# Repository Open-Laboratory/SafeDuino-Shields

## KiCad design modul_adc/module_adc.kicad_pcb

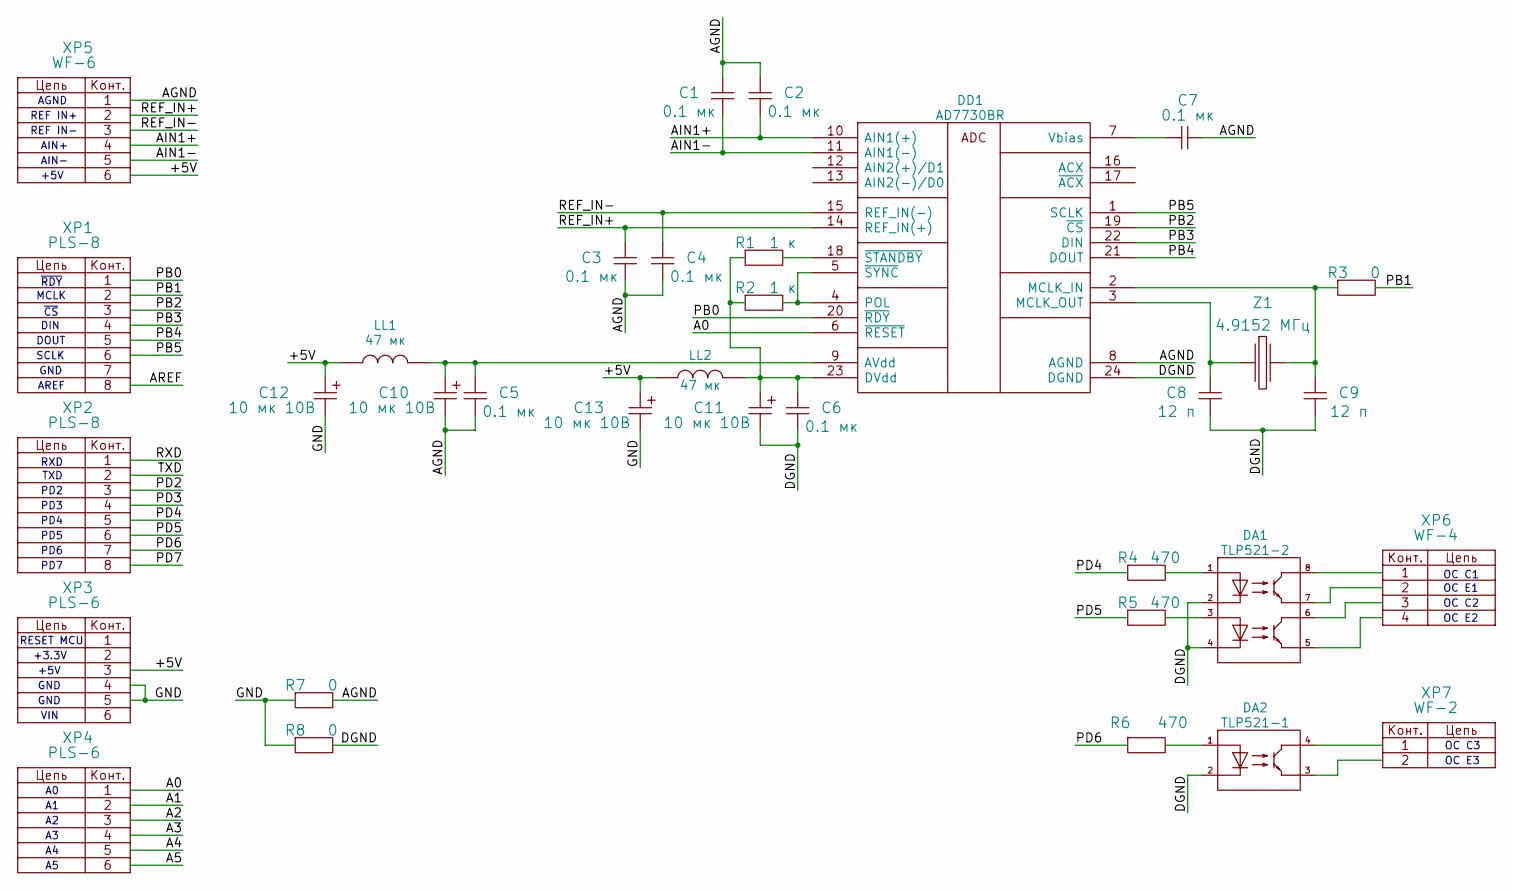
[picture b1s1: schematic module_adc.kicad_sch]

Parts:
C1, C2, C3, C4, C5, C6, C7: 0.1 мк; SMD0805
C8, C9: 12 п; SMD0805
C10, C11, C12, C13: 10 мк 10В; CASE_B
DA1: TLP521-2; DIP_8
DA2: TLP521-1; DIP_4
DD1: AD7730BR; SOIC_24
LL1, LL2: 47 мк; SMD0805
R1, R2: 1 к; SMD0805
R3, R7, R8: 0; SMD0805
R4, R5, R6: 470; SMD0805
XP1, XP2: PLS-8; PIN_ARRAY_8x1
XP3, XP4: PLS-6; PIN_ARRAY_6x1
XP5: WF-6
XP6: WF-4
XP7: WF-2
Z1: 4.9152 МГц; HC-49U

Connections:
/+5V: C12.1, C13.1, LL1.2, LL2.2, XP3.3, XP5.6
/A0: DD1.6 (~RESET), XP4.1
/A1: XP4.2
/A2: XP4.3
/A3: XP4.4
/A4: XP4.5
/A5: XP4.6
/AGND: C1.1, C2.1, C3.2, C4.2, C5.2, C7.1, C10.2, DD1.8 (AGND), R7.2, XP5.1
/AIN1+: C2.2, DD1.10 (AIN1(+)), XP5.4
/AIN1-: C1.2, DD1.11 (AIN1(-)), XP5.5
/AREF: XP1.8
/DGND: C6.2, C8.2, C9.2, C11.2, DA1.2, DA1.4, DA2.2, DD1.24 (DGND), R8.2
/GND: C12.2, C13.2, R7.1, R8.1, XP3.4, XP3.5
/PB0: DD1.20 (~RDY), XP1.1
/PB1: R3.2, XP1.2
/PB2: DD1.19 (~CS), XP1.3
/PB3: DD1.22 (DIN), XP1.4
/PB4: DD1.21 (DOUT), XP1.5
/PB5: DD1.1 (SCLK), XP1.6
/PD2: XP2.3
/PD3: XP2.4
/PD4: R4.1, XP2.5
/PD5: R5.1, XP2.6
/PD6: R6.1, XP2.7
/PD7: XP2.8
/REF_IN+: C3.1, DD1.14 (REF_IN(+)), XP5.2
/REF_IN-: C4.1, DD1.15 (REF_IN(-)), XP5.3
/RXD: XP2.1
/TXD: XP2.2
unnamed: DA1.1, R4.2
unnamed: DA1.3, R5.2
unnamed: DA1.5, XP6.4
unnamed: DA1.6, XP6.3
unnamed: DA1.7, XP6.2
unnamed: DA1.8, XP6.1
unnamed: DA2.1, R6.2
unnamed: DA2.3, XP7.2
unnamed: DA2.4, XP7.1
unnamed: C5.1, C10.1, DD1.9 (AVdd), LL1.1
unnamed: C6.1, C11.1, DD1.23 (DVdd), LL2.1, R1.1, R2.1
unnamed: C9.1, DD1.2 (MCLK_IN), R3.1, Z1.2
unnamed: C8.1, DD1.3 (MCLK_OUT), Z1.1
unnamed: DD1.4 (POL), DD1.5 (~SYNC), R2.2
unnamed: C7.2, DD1.7 (Vbias)
unnamed: DD1.18 (~STANDBY), R1.2

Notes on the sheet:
RESET MCU
PD7
PD4
+5V
OC E2
MCLK
OC C3
RXD
REF IN-
TXD
PD6
PD2
OC E1
AGND
VIN
GND
OC C1
AREF
~{CS}
OC E3
AIN-
OC C2
DOUT
AIN+
DIN
PD3
~{RDY}
PD5
+3.3V
REF IN+
SCLK

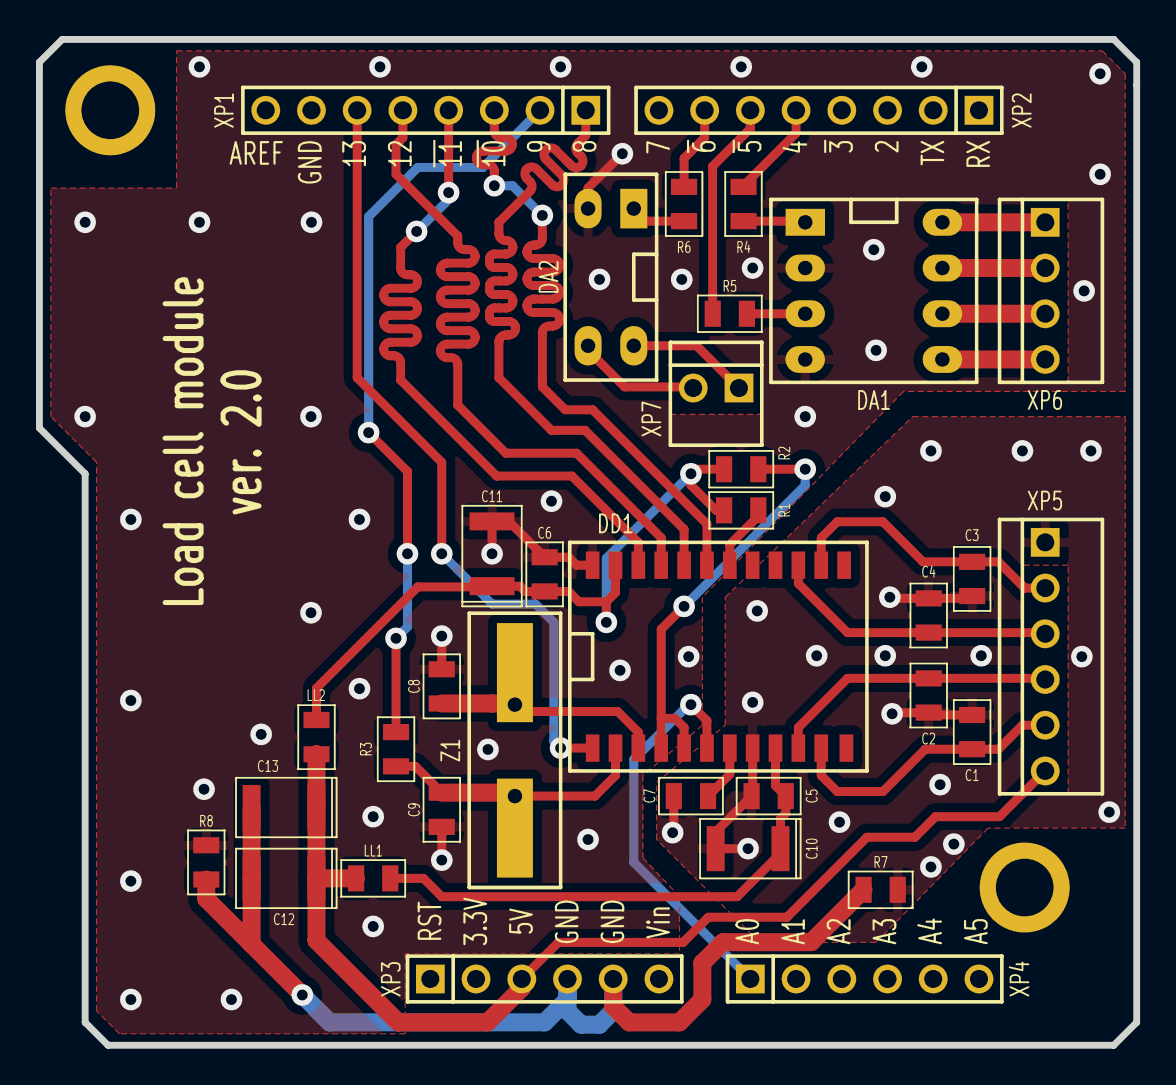
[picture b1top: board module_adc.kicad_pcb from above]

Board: 2 copper layers, 61.0 x 55.9 mm, 36 parts (0 on the bottom side), 34 nets.

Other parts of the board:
1_PIN_3_2mm_1, 1_PIN_3_2mm_2: P***; 1_pin_3_2mm

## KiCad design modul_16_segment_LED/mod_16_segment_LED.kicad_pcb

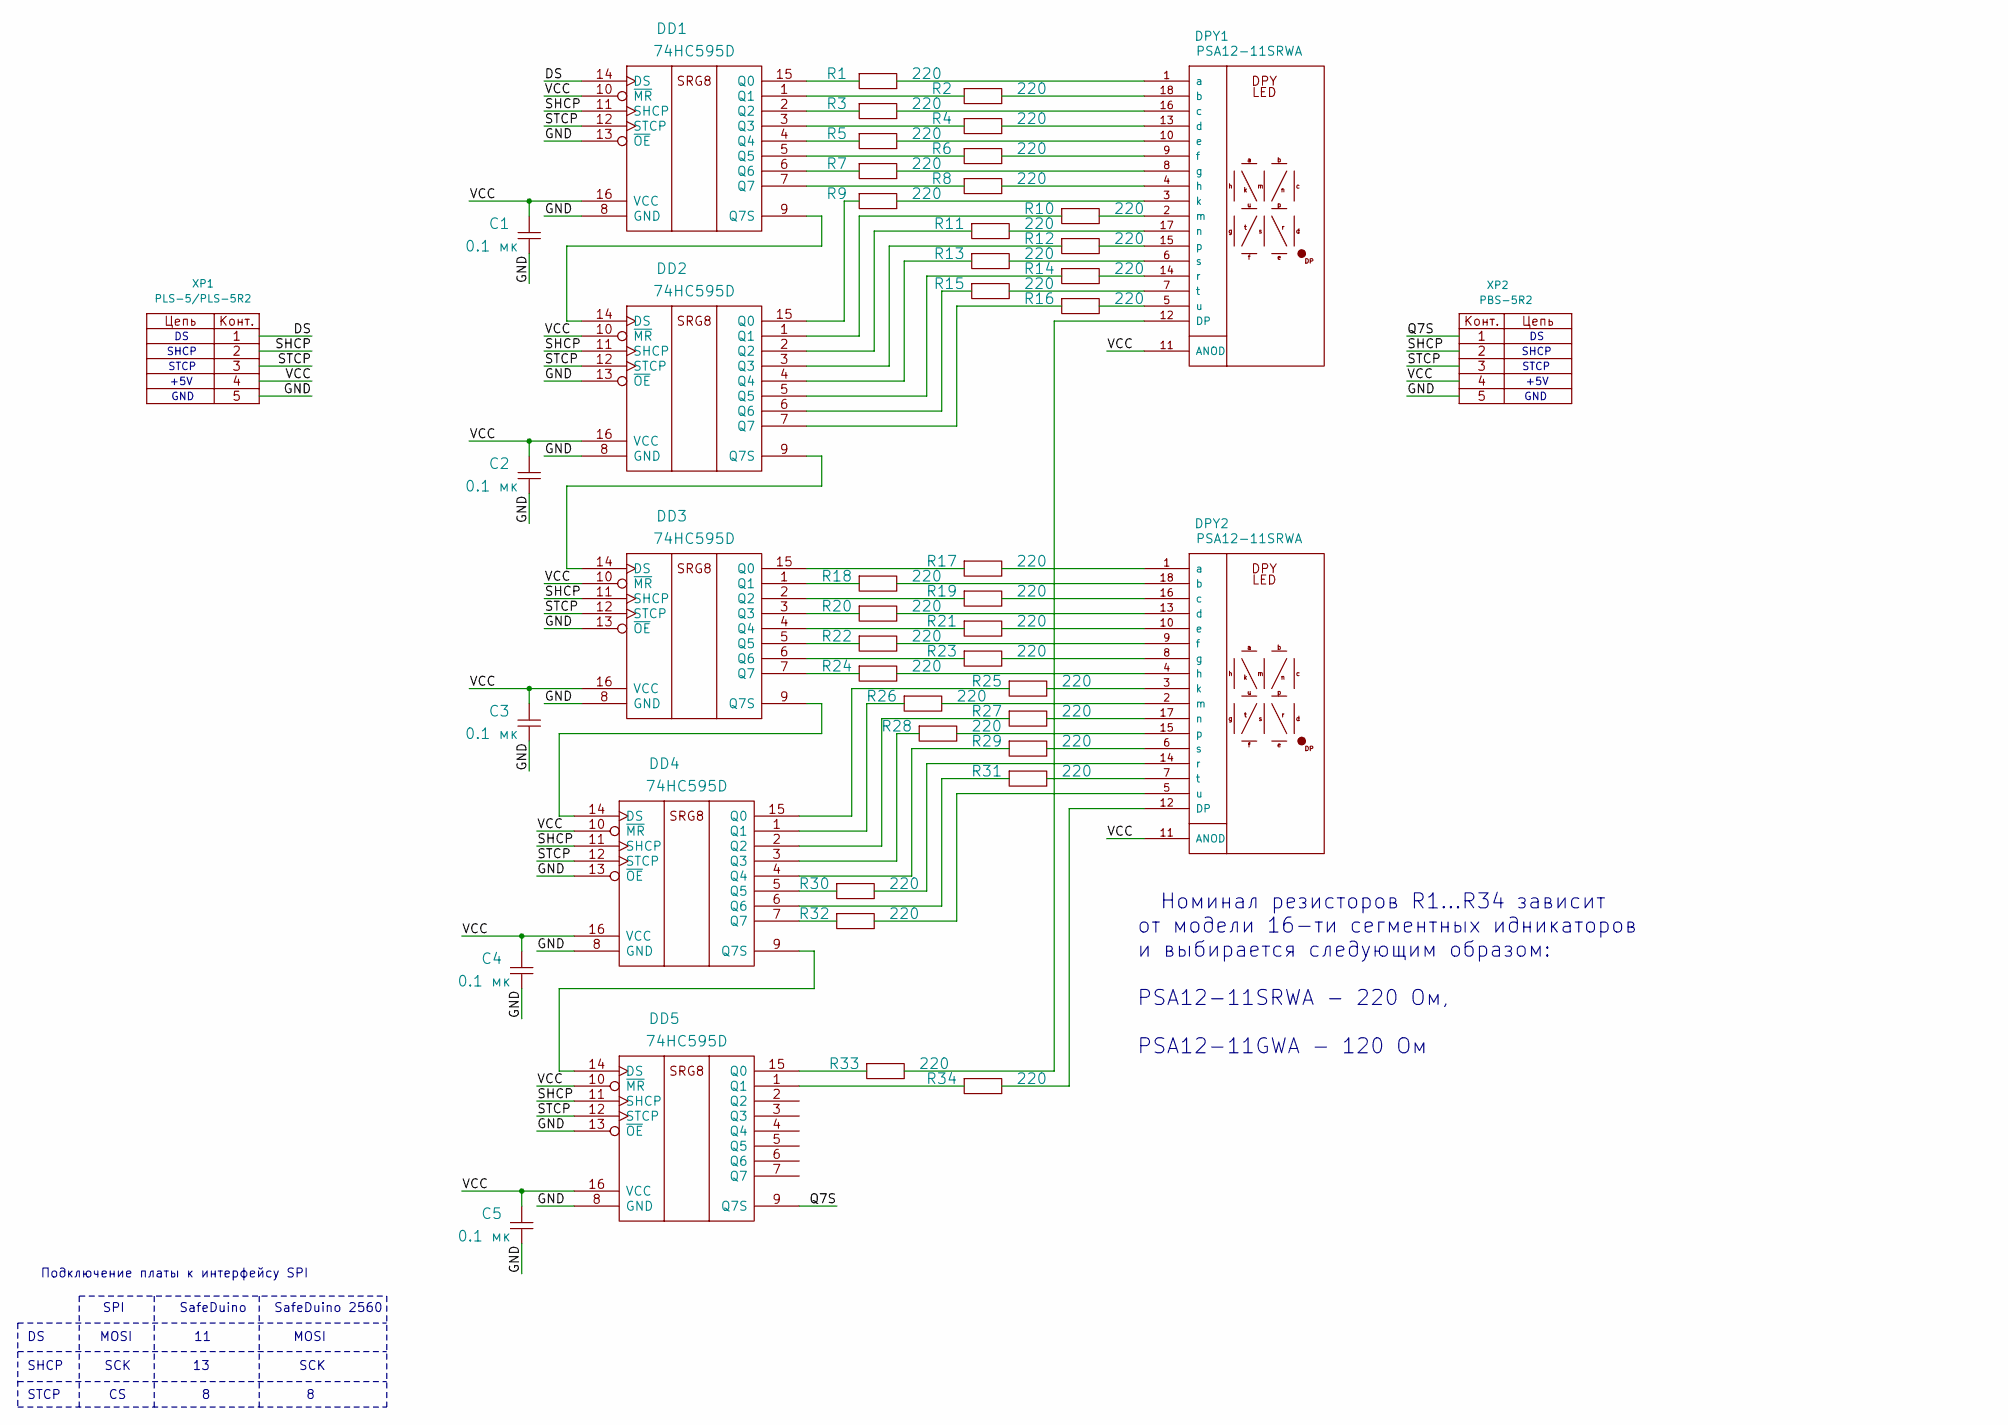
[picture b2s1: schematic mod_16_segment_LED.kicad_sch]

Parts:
C1, C2, C3, C4, C5: 0.1 мк; SMD0805
DD1, DD2, DD3, DD4, DD5: 74HC595D; SOIC16
DPY1, DPY2: PSA12-11SRWA; PSA12-11
R1, R2, R3, R4, R5, R6, R7, R8, R9, R10, R11, R12, R13, R14, R15, R16, R17, R18, R19, R20, R21, R22, R23, R24, R25, R26, R27, R28, R29, R30, R31, R32, R33, R34: 220; SMD0805
XP1: PLS-5/PLS-5R2; PIN_ARRAY_5x1
XP2: PBS-5R2; PIN_ARRAY_5x1

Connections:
/DS: DD1.14 (DS), XP1.1
/GND: C1.1, C2.1, C3.1, C4.1, C5.1, DD1.8 (GND), DD1.13 (~OE), DD2.8 (GND), DD2.13 (~OE), DD3.8 (GND), DD3.13 (~OE), DD4.8 (GND), DD4.13 (~OE), DD5.8 (GND), DD5.13 (~OE), XP1.5, XP2.5
/Q7S: DD5.9 (Q7S), XP2.1
/SHCP: DD1.11 (SHCP), DD2.11 (SHCP), DD3.11 (SHCP), DD4.11 (SHCP), DD5.11 (SHCP), XP1.2, XP2.2
/STCP: DD1.12 (STCP), DD2.12 (STCP), DD3.12 (STCP), DD4.12 (STCP), DD5.12 (STCP), XP1.3, XP2.3
/VCC: C1.2, C2.2, C3.2, C4.2, C5.2, DD1.10 (~MR), DD1.16 (VCC), DD2.10 (~MR), DD2.16 (VCC), DD3.10 (~MR), DD3.16 (VCC), DD4.10 (~MR), DD4.16 (VCC), DD5.10 (~MR), DD5.16 (VCC), DPY1.11 (ANOD), DPY2.11 (ANOD), XP1.4, XP2.4
unnamed: DD1.15 (Q0), R1.1
unnamed: DD1.1 (Q1), R2.1
unnamed: DD1.2 (Q2), R3.1
unnamed: DD1.3 (Q3), R4.1
unnamed: DD1.4 (Q4), R5.1
unnamed: DD1.5 (Q5), R6.1
unnamed: DD1.6 (Q6), R7.1
unnamed: DD1.7 (Q7), R8.1
unnamed: DD1.9 (Q7S), DD2.14 (DS)
unnamed: DD2.15 (Q0), R9.1
unnamed: DD2.1 (Q1), R10.1
unnamed: DD2.2 (Q2), R11.1
unnamed: DD2.3 (Q3), R12.1
unnamed: DD2.4 (Q4), R13.1
unnamed: DD2.5 (Q5), R14.1
unnamed: DD2.6 (Q6), R15.1
unnamed: DD2.7 (Q7), R16.1
unnamed: DD2.9 (Q7S), DD3.14 (DS)
unnamed: DD3.15 (Q0), R17.1
unnamed: DD3.1 (Q1), R18.1
unnamed: DD3.2 (Q2), R19.1
unnamed: DD3.3 (Q3), R20.1
unnamed: DD3.4 (Q4), R21.1
unnamed: DD3.5 (Q5), R22.1
unnamed: DD3.6 (Q6), R23.1
unnamed: DD3.7 (Q7), R24.1
unnamed: DD3.9 (Q7S), DD4.14 (DS)
unnamed: DD4.15 (Q0), R25.1
unnamed: DD4.1 (Q1), R26.1
unnamed: DD4.2 (Q2), R27.1
unnamed: DD4.3 (Q3), R28.1
unnamed: DD4.4 (Q4), R29.1
unnamed: DD4.5 (Q5), R30.1
unnamed: DD4.6 (Q6), R31.1
unnamed: DD4.7 (Q7), R32.1
unnamed: DD4.9 (Q7S), DD5.14 (DS)
unnamed: DD5.15 (Q0), R33.1
unnamed: DD5.1 (Q1), R34.1
unnamed: DPY1.12 (DP), R33.2
unnamed: DPY1.1 (a), R1.2
unnamed: DPY1.18 (b), R2.2
unnamed: DPY1.16 (c), R3.2
unnamed: DPY1.13 (d), R4.2
unnamed: DPY1.10 (e), R5.2
unnamed: DPY1.9 (f), R6.2
unnamed: DPY1.8 (g), R7.2
unnamed: DPY1.4 (h), R8.2
unnamed: DPY1.3 (k), R9.2
unnamed: DPY1.2 (m), R10.2
unnamed: DPY1.17 (n), R11.2
unnamed: DPY1.15 (p), R12.2
unnamed: DPY1.14 (r), R14.2
unnamed: DPY1.6 (s), R13.2
unnamed: DPY1.7 (t), R15.2
unnamed: DPY1.5 (u), R16.2
unnamed: DPY2.12 (DP), R34.2
unnamed: DPY2.1 (a), R17.2
unnamed: DPY2.18 (b), R18.2
unnamed: DPY2.16 (c), R19.2
unnamed: DPY2.13 (d), R20.2
unnamed: DPY2.10 (e), R21.2
unnamed: DPY2.9 (f), R22.2
unnamed: DPY2.8 (g), R23.2
unnamed: DPY2.4 (h), R24.2
unnamed: DPY2.3 (k), R25.2
unnamed: DPY2.2 (m), R26.2
unnamed: DPY2.17 (n), R27.2
unnamed: DPY2.15 (p), R28.2
unnamed: DPY2.14 (r), R30.2
unnamed: DPY2.6 (s), R29.2
unnamed: DPY2.7 (t), R31.2
unnamed: DPY2.5 (u), R32.2

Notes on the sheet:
SPI SafeDuino SafeDuino 2560 DS MOSI 11 MOSI SHCP SCK 13 SCK STCP CS 8 8
GND
SHCP
+5V
STCP
Номинал резисторов R1...R34 зависит от модели 16-ти сегментных идникаторов и выбирается следующим образом: PSA12-11SRWA - 220 Ом, PSA12-11GWA - 120 Ом
Подключение платы к интерфейсу SPI

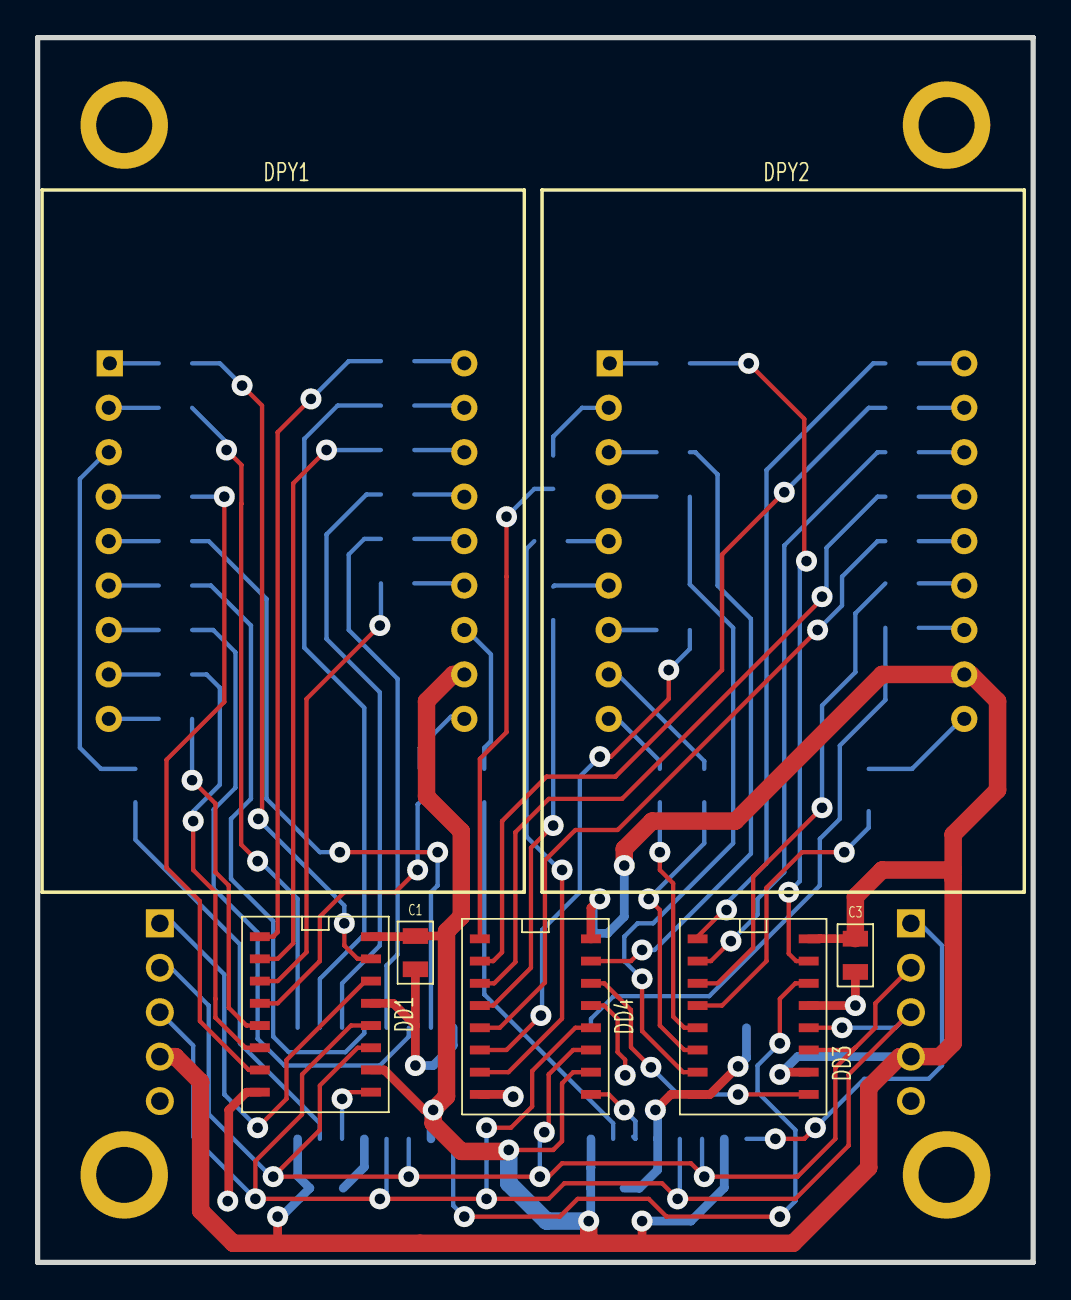
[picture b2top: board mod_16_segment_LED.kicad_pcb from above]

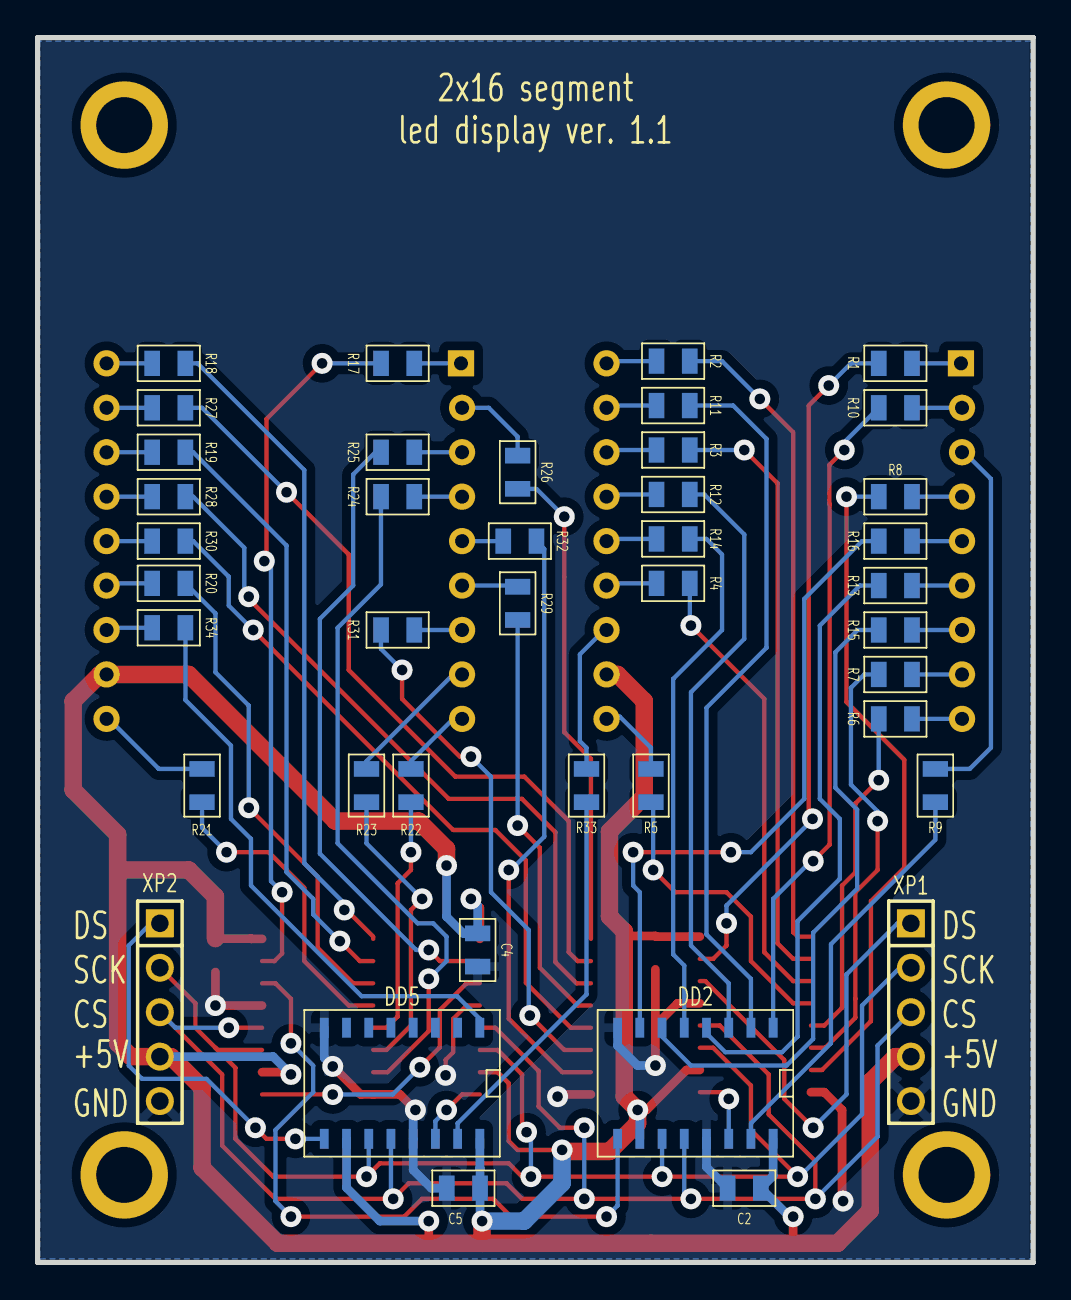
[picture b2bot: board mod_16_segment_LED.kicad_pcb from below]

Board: 2 copper layers, 56.9 x 70.0 mm, 52 parts (41 on the bottom side), 78 nets.

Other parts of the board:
PIN1, PIN2, PIN3, PIN4: P***; 1_pin_3_2mm

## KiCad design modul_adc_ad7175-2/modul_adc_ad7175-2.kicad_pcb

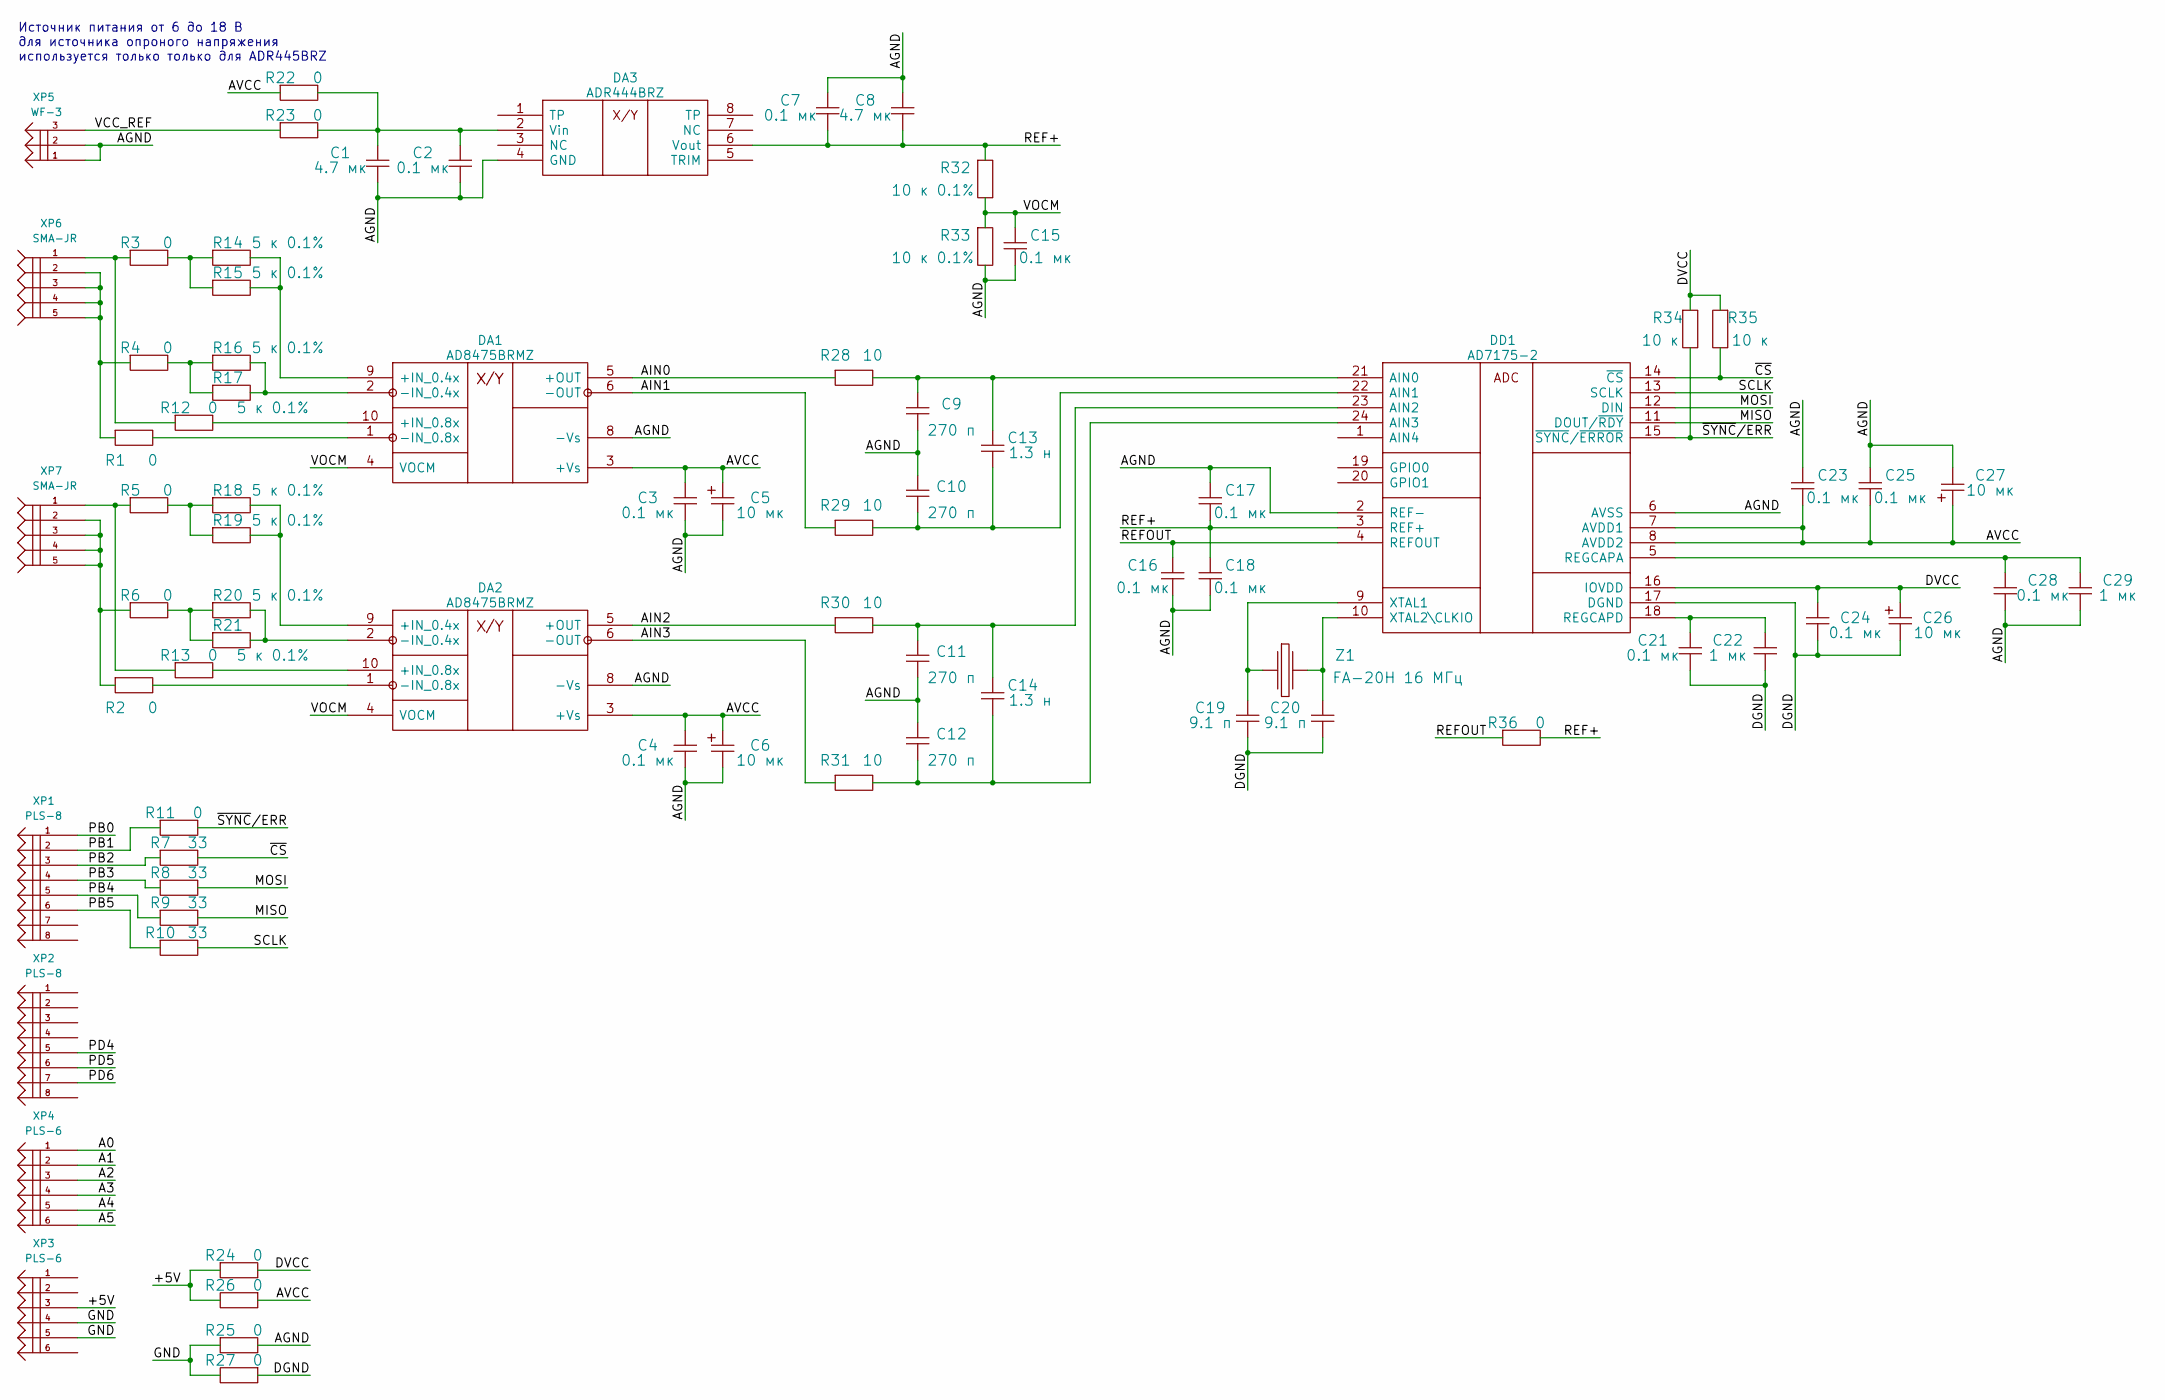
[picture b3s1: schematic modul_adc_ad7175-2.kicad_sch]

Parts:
C1, C8: 4.7 мк; SMD0805
C2, C3, C4, C7, C15, C16, C17, C18, C21, C23, C24, C25, C28: 0.1 мк; SMD0805
C5, C6, C26, C27: 10 мк; CASE_B
C9, C10, C11, C12: 270 п; SMD0805
C13, C14: 1.3 н; SMD0805
C19, C20: 9.1 п; SMD0805
C22, C29: 1 мк; SMD0805
DA1, DA2: AD8475BRMZ; MSOP-10
DA3: ADR444BRZ; SOIC8
DD1: AD7175-2; TSOP24
R1, R2, R3, R4, R5, R6, R11, R12, R13, R22, R23, R24, R25, R26, R27, R36: 0; SMD0805
R7, R8, R9, R10: 33; SMD0805
R14, R15, R16, R17, R18, R19, R20, R21: 5 к 0.1%; SMD0805
R28, R29, R30, R31: 10; SMD0805
R32, R33: 10 к 0.1%; SMD0805
R34, R35: 10 к; SMD0805
XP1, XP2: PLS-8; PIN_ARRAY_8x1
XP3, XP4: PLS-6; PIN_ARRAY_6x1
XP5: WF-3
XP6, XP7: SMA-JR; SMA-R
Z1: FA-20H 16 МГц; EPSON_FA-20H

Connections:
/+5V: R24.1, R26.2, XP3.3
/A0: XP4.1
/A1: XP4.2
/A2: XP4.3
/A3: XP4.4
/A4: XP4.5
/A5: XP4.6
/AGND: C1.2, C2.2, C3.2, C4.2, C5.2, C6.2, C7.1, C8.1, C9.2, C10.1, C11.2, C12.1, C15.2, C16.2, C17.1, C18.2, C23.1, C25.1, C27.2, C28.2, C29.2, DA1.8 (-Vs), DA2.8 (-Vs), DA3.4 (GND), DD1.2 (REF-), DD1.6 (AVSS), R25.2, R33.2, XP5.1, XP5.2
/AIN0: DA1.5 (+OUT), R28.1
/AIN1: DA1.6 (-OUT), R29.1
/AIN2: DA2.5 (+OUT), R30.1
/AIN3: DA2.6 (-OUT), R31.1
/AVCC: C3.1, C4.1, C5.1, C6.1, C23.2, C25.2, C27.1, DA1.3 (+Vs), DA2.3 (+Vs), DD1.7 (AVDD1), DD1.8 (AVDD2), R22.1, R26.1
/DGND: C19.2, C20.2, C21.2, C22.2, C24.2, C26.2, DD1.17 (DGND), R27.1
/DVCC: C24.1, C26.1, DD1.16 (IOVDD), R24.2, R34.1, R35.1
/GND: R25.1, R27.2, XP3.4, XP3.5
/MISO: DD1.11 (DOUT/~RDY), R9.2
/MOSI: DD1.12 (DIN), R8.2
/PB0: XP1.1
/PB1: R11.1, XP1.2
/PB2: R7.1, XP1.3
/PB3: R8.1, XP1.4
/PB4: R9.1, XP1.5
/PB5: R10.1, XP1.6
/PD4: XP2.5
/PD5: XP2.6
/PD6: XP2.7
/REF+: C7.2, C8.2, C17.2, C18.1, DA3.6 (Vout), DD1.3 (REF+), R32.1, R36.2
/REFOUT: C16.1, DD1.4 (REFOUT), R36.1
/SCLK: DD1.13 (SCLK), R10.2
/VCC_REF: R23.1, XP5.3
/VOCM: C15.1, DA1.4 (VOCM), DA2.4 (VOCM), R32.2, R33.1
/~CS: DD1.14 (~CS), R7.2, R35.2
/~SYNC/ERR: DD1.15 (~SYNC/~ERROR), R11.2, R34.2
unnamed: C1.1, C2.1, DA3.2 (Vin), R22.2, R23.2
unnamed: C10.2, C13.2, DD1.22 (AIN1), R29.2
unnamed: C11.1, C14.1, DD1.23 (AIN2), R30.2
unnamed: C12.2, C14.2, DD1.24 (AIN3), R31.2
unnamed: C9.1, C13.1, DD1.21 (AIN0), R28.2
unnamed: C19.1, DD1.9 (XTAL1), Z1.1
unnamed: C20.1, DD1.10 (XTAL2\CLKIO), Z1.2
unnamed: C21.1, C22.1, DD1.18 (REGCAPD)
unnamed: C28.1, C29.1, DD1.5 (REGCAPA)
unnamed: DA1.1 (-IN_0.8x), R1.2
unnamed: DA1.2 (-IN_0.4x), R16.2, R17.2
unnamed: DA1.9 (+IN_0.4x), R14.2, R15.2
unnamed: DA1.10 (+IN_0.8x), R12.2
unnamed: DA2.1 (-IN_0.8x), R2.2
unnamed: DA2.2 (-IN_0.4x), R20.2, R21.2
unnamed: DA2.9 (+IN_0.4x), R18.2, R19.2
unnamed: DA2.10 (+IN_0.8x), R13.2
unnamed: R1.1, R4.1, XP6.2, XP6.3, XP6.4, XP6.5
unnamed: R2.1, R6.1, XP7.2, XP7.3, XP7.4, XP7.5
unnamed: R3.1, R12.1, XP6.1
unnamed: R5.1, R13.1, XP7.1
unnamed: R3.2, R14.1, R15.1
unnamed: R4.2, R16.1, R17.1
unnamed: R5.2, R18.1, R19.1
unnamed: R6.2, R20.1, R21.1

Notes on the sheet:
Источник питания от 6 до 18 В для источника опроного напряжения используется только только для ADR445BRZ

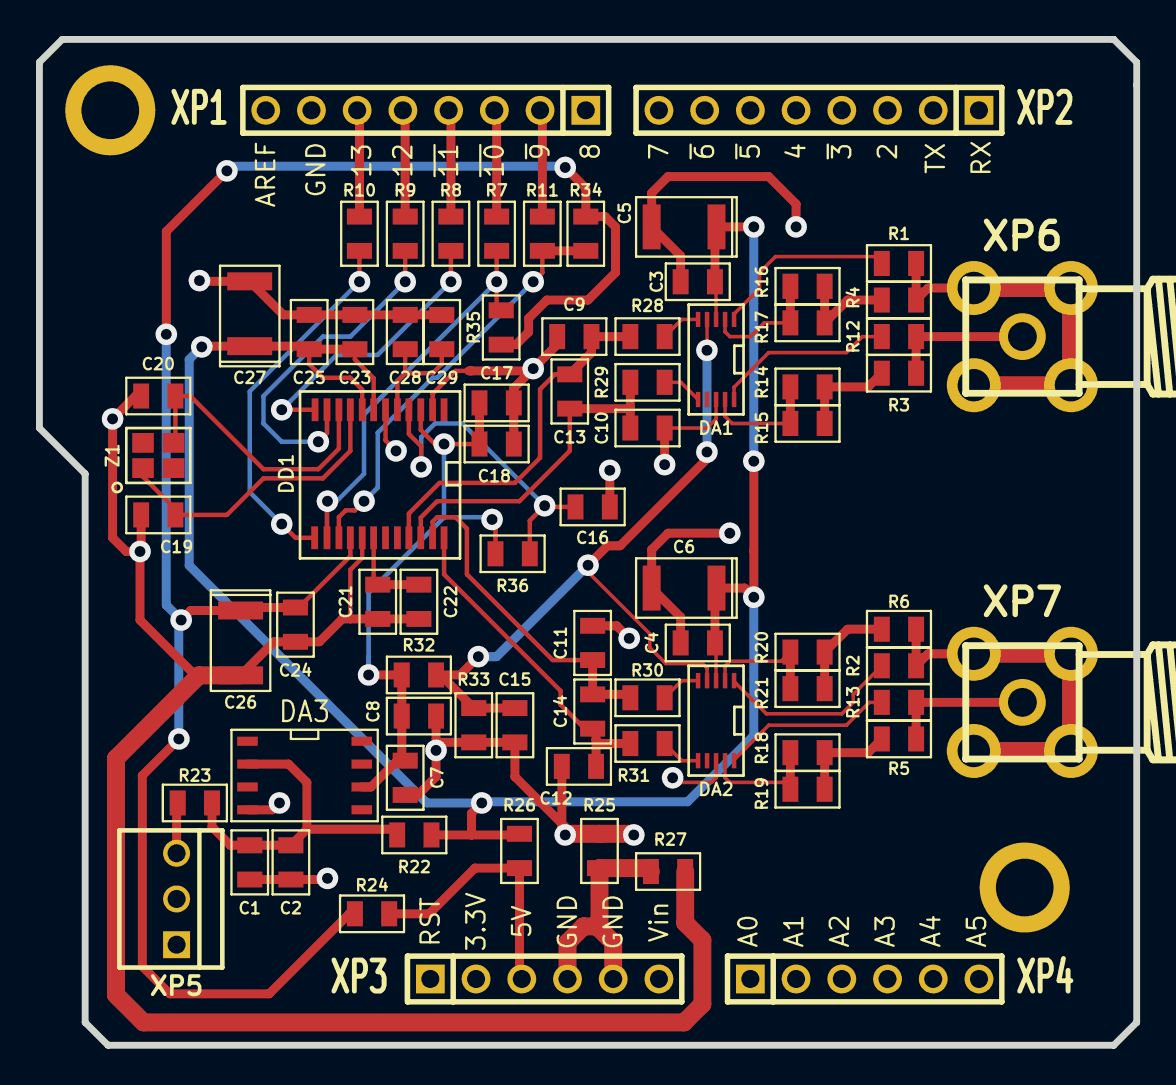
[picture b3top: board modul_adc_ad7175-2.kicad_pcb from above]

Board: 2 copper layers, 61.0 x 55.9 mm, 79 parts (0 on the bottom side), 49 nets.

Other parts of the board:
arduino: P***; 1_pin
arduino#2: P***; 1_pin

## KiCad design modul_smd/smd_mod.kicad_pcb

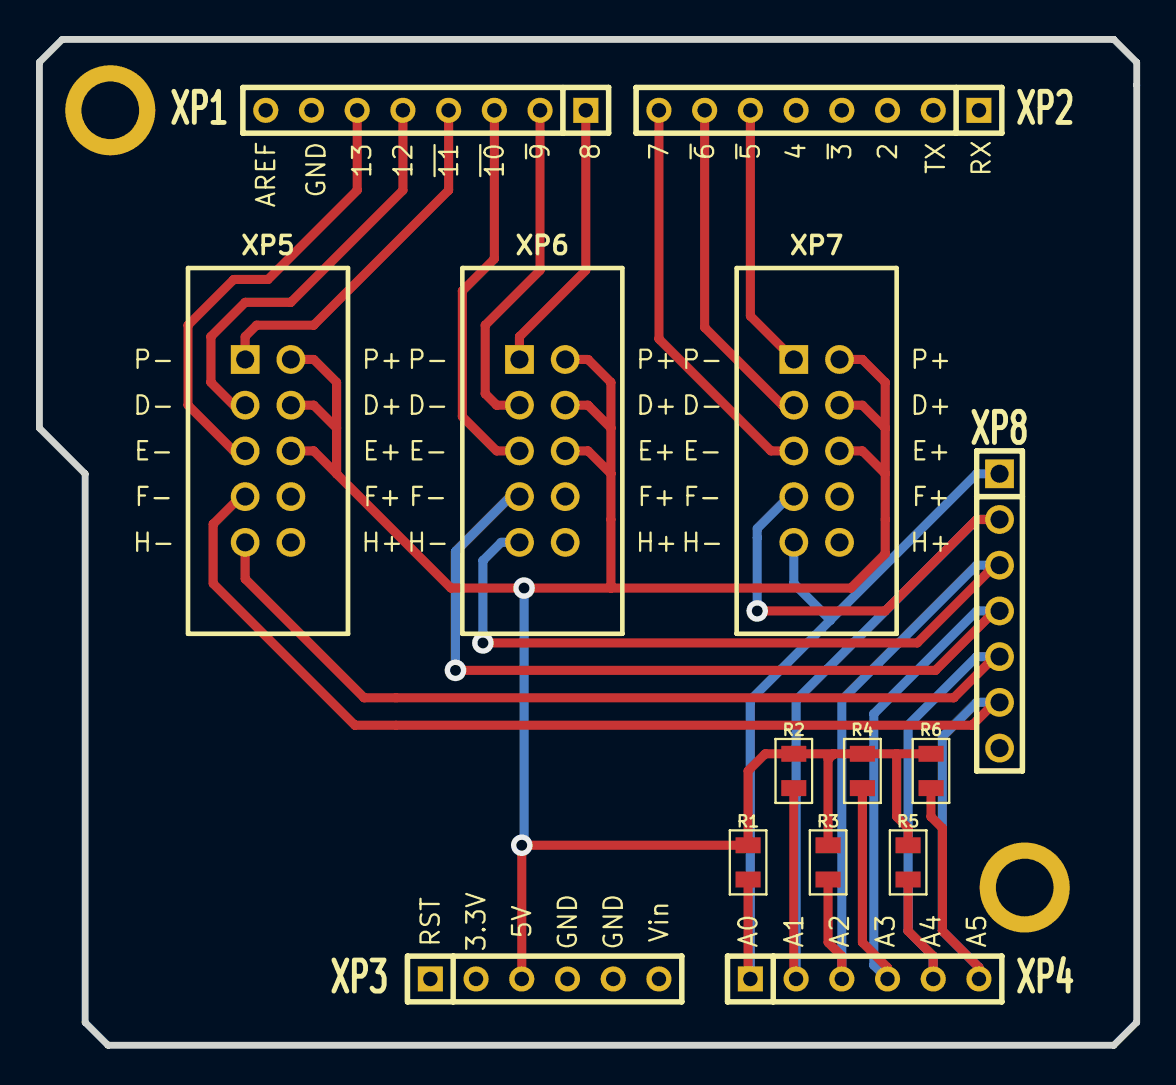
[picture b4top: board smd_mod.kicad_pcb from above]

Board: 2 copper layers, 61.0 x 55.9 mm, 16 parts (0 on the bottom side), 17 nets.

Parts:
R1, R2, R3, R4, R5, R6: 1_k; SMD0805
XP1, XP2: PBS-8; SIL-8
XP3, XP4: PBS-6; SIL-6
XP5, XP6, XP7: IDC-10MS
XP8: WF-7; SIL-7
arduino: P***; 1_pin
arduino#2: P***; 1_pin

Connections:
/+5V: R1.2, R2.2, R3.2, R4.1, R5.1, R6.1, XP3.3, XP5.2, XP5.4, XP5.6, XP6.2, XP6.4, XP6.6, XP7.2, XP7.4, XP7.6
/GND: XP1.7, XP3.4, XP3.5, XP5.8, XP5.10, XP6.8, XP6.10, XP7.8, XP7.10, XP8.7
/PB0: XP1.1, XP6.1
/PB1: XP1.2, XP6.3
/PB2: XP1.3, XP6.5
/PB3: XP1.4, XP5.1
/PB4: XP1.5, XP5.3
/PB5: XP1.6, XP5.5
/PC0: R1.1, XP4.1, XP7.9, XP8.1
/PC1: R2.1, XP4.2, XP7.7, XP8.2
/PC2: R3.1, XP4.3, XP6.9, XP8.3
/PC3: R4.2, XP4.4, XP6.7, XP8.4
/PC4: R5.2, XP4.5, XP5.9, XP8.5
/PC5: R6.2, XP4.6, XP5.7, XP8.6
/PD5: XP2.6, XP7.1
/PD6: XP2.7, XP7.3
/PD7: XP2.8, XP7.5

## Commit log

2015-11-05 First commit.
2015-11-06 Поправил шелкографию и добавил номиналы у элементов для adc_module.
2016-01-21 Добавил таблицу для подключения платы 16_segment_LED к SPI.
2017-09-22 Поправил название микросхемы 74HC595B на 74HC595D.
2018-03-24 Добавил проект печатной платы с АЦП AD7175-2.
2018-04-07 Подготовил печатную плату к разводке.
2018-04-11 Приступил к разводке платы c AD7175-2.
2018-04-13 Закончил разводку платы c AD7175-2.
2018-04-24 Добавил проект печатный платы для энкодера ALPS EC11E.
2018-04-25 Добавил проект платы измерителя тока.
2018-04-26 Отправил платы АЦП AD7175-2, энкодера и измерителя тока в производство.
2018-12-29 Добавил номиналы резисторов подключенных последовательно SPI для АЦП AD7175-2.
2023-07-11 Перевёл проект на Kicad 6.0
2023-07-11 Добавли файлы.
2023-07-11 Добавли файл.
2023-07-26 Перевёл плату энкодера под kicad 6.0. Добавли описание к с схемой и программой.
2023-07-26 Поправил схему во вложении.
2023-08-10 Поправил и дополнил программу для тестирования энкодера.
2024-12-04 Перевёл проект на kicad 7.0 и внёс небольшие правки в обозначениях на схеме.
2025-02-06 Добавил дополнительные резисторы в схему16-ти сегментного индикатора.
2025-02-07 Исправил на плате 16-ти сегментного индикатора размеры контуров платы и крепёжных отверстий.
2025-02-10 Восстановил проект для работы в kicad 7.0.
2025-02-10 Дополнил схему ацп для тензодатчика и приступил к трассировке печатной платы.
2025-02-11 Подготовил печатные платы тензодатчика и 16-ти сегментного индикатора к отправке в производство.
2025-02-13 Добавил обозначение разъёмов на схеме, поправил посадочное место кварца и отправил плату в производство.
